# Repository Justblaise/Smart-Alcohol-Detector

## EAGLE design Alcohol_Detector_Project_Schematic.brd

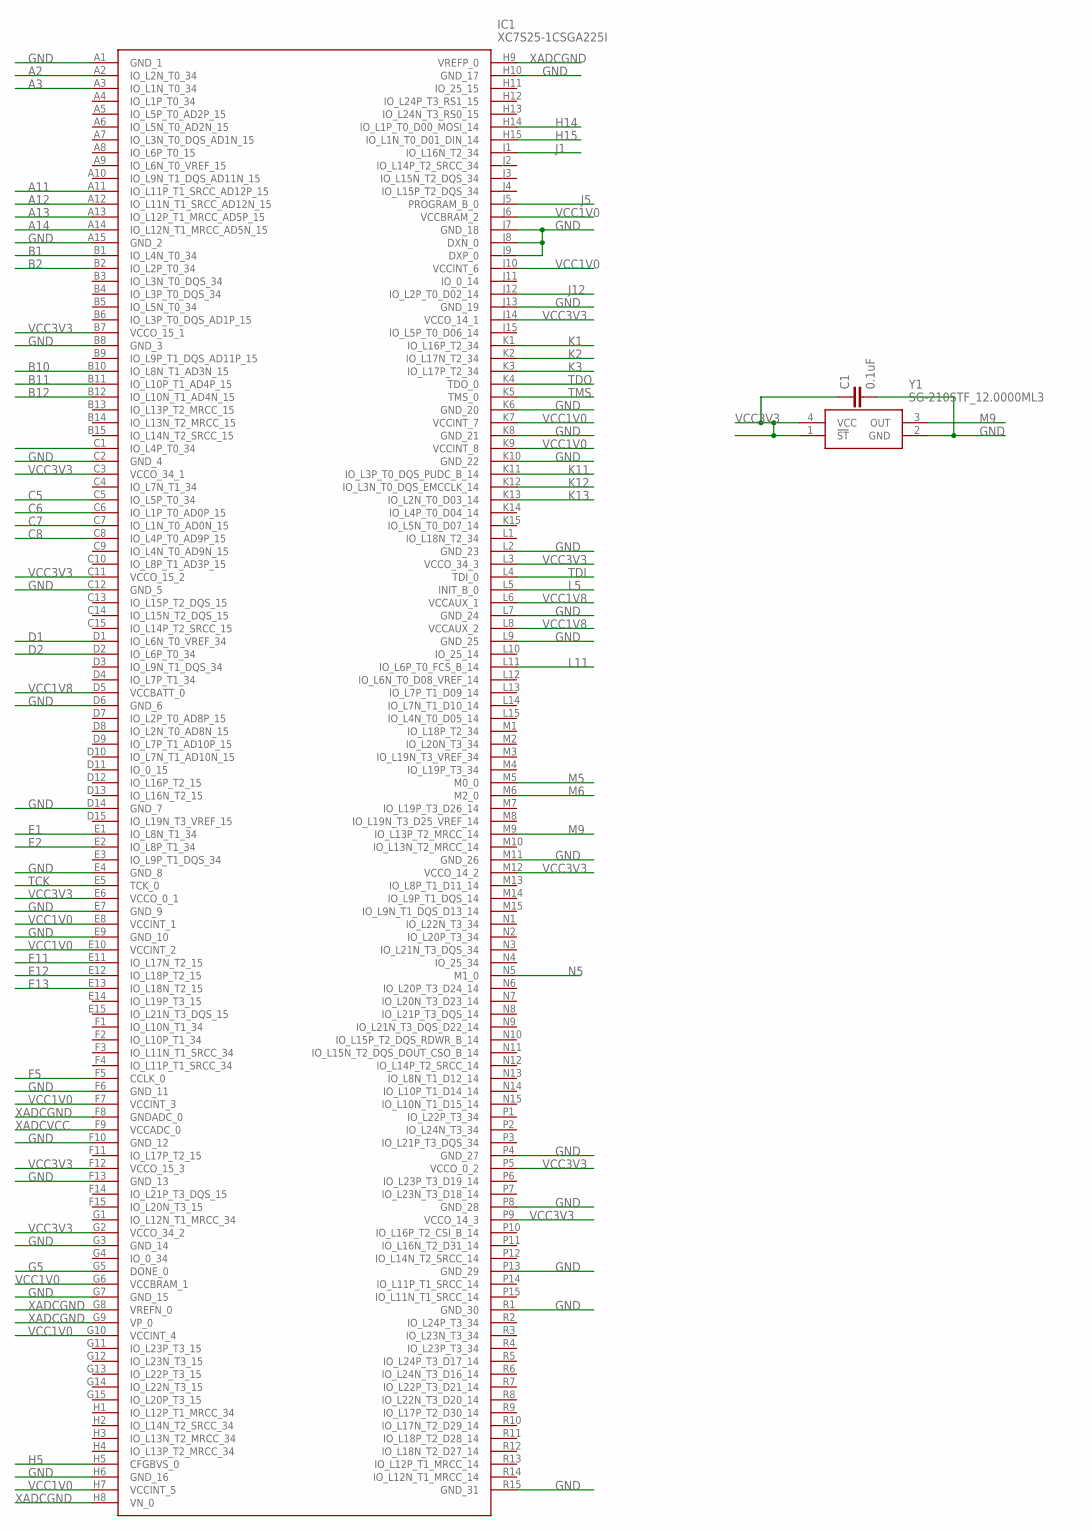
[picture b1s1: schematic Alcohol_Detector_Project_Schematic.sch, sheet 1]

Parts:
C1: 0.1uF; 0402
IC1: XC7S25-1CSGA225I; BGA225C80P15X15_1300X1300X140
Y1: SG-210STF_12.0000ML3; SG210STF120000ML3

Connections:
A2: IC1.A2 (IO_L2N_T0_34); also elsewhere on the board
A3: IC1.A3 (IO_L1N_T0_34); also elsewhere on the board
A11: IC1.A11 (IO_L11P_T1_SRCC_AD12P_15); also elsewhere on the board
A12: IC1.A12 (IO_L11N_T1_SRCC_AD12N_15); also elsewhere on the board
A13: IC1.A13 (IO_L12P_T1_MRCC_AD5P_15); also elsewhere on the board
A14: IC1.A14 (IO_L12N_T1_MRCC_AD5N_15); also elsewhere on the board
B1: IC1.B1 (IO_L4N_T0_34); also elsewhere on the board
B2: IC1.B2 (IO_L2P_T0_34); also elsewhere on the board
B10: IC1.B10 (IO_L8N_T1_AD3N_15); also elsewhere on the board
B11: IC1.B11 (IO_L10P_T1_AD4P_15); also elsewhere on the board
B12: IC1.B12 (IO_L10N_T1_AD4N_15); also elsewhere on the board
C5: IC1.C5 (IO_L5P_T0_34); also elsewhere on the board
C6: IC1.C6 (IO_L1P_T0_AD0P_15); also elsewhere on the board
C7: IC1.C7 (IO_L1N_T0_AD0N_15); also elsewhere on the board
C8: IC1.C8 (IO_L4P_T0_AD9P_15); also elsewhere on the board
D1: IC1.D1 (IO_L6N_T0_VREF_34); also elsewhere on the board
D2: IC1.D2 (IO_L6P_T0_34); also elsewhere on the board
E1: IC1.E1 (IO_L8N_T1_34); also elsewhere on the board
E2: IC1.E2 (IO_L8P_T1_34); also elsewhere on the board
E11: IC1.E11 (IO_L17N_T2_15); also elsewhere on the board
E12: IC1.E12 (IO_L18P_T2_15); also elsewhere on the board
E13: IC1.E13 (IO_L18N_T2_15); also elsewhere on the board
F5: IC1.F5 (CCLK_0); also elsewhere on the board
G5: IC1.G5 (DONE_0); also elsewhere on the board
GND: C1.2, IC1.A1 (GND_1), IC1.A15 (GND_2), IC1.B8 (GND_3), IC1.C2 (GND_4), IC1.C12 (GND_5), IC1.D6 (GND_6), IC1.D14 (GND_7), IC1.E4 (GND_8), IC1.E7 (GND_9), IC1.E9 (GND_10), IC1.F6 (GND_11), IC1.F10 (GND_12), IC1.F13 (GND_13), IC1.G3 (GND_14), IC1.G7 (GND_15), IC1.H6 (GND_16), IC1.H10 (GND_17), IC1.J7 (GND_18), IC1.J8 (DXN_0), IC1.J9 (DXP_0), IC1.J13 (GND_19), IC1.K6 (GND_20), IC1.K8 (GND_21), IC1.K10 (GND_22), IC1.L2 (GND_23), IC1.L7 (GND_24), IC1.L9 (GND_25), IC1.M11 (GND_26), IC1.P4 (GND_27), IC1.P8 (GND_28), IC1.P13 (GND_29), IC1.R1 (GND_30), IC1.R15 (GND_31), Y1.2 (GND); also elsewhere on the board
H5: IC1.H5 (CFGBVS_0); also elsewhere on the board
H14: IC1.H14 (IO_L1P_T0_D00_MOSI_14); also elsewhere on the board
H15: IC1.H15 (IO_L1N_T0_D01_DIN_14); also elsewhere on the board
J1: IC1.J1 (IO_L16N_T2_34); also elsewhere on the board
J5: IC1.J5 (PROGRAM_B_0); also elsewhere on the board
J12: IC1.J12 (IO_L2P_T0_D02_14); also elsewhere on the board
K1: IC1.K1 (IO_L16P_T2_34); also elsewhere on the board
K2: IC1.K2 (IO_L17N_T2_34); also elsewhere on the board
K3: IC1.K3 (IO_L17P_T2_34); also elsewhere on the board
K11: IC1.K11 (IO_L3P_T0_DQS_PUDC_B_14); also elsewhere on the board
K12: IC1.K12 (IO_L3N_T0_DQS_EMCCLK_14); also elsewhere on the board
K13: IC1.K13 (IO_L2N_T0_D03_14); also elsewhere on the board
L5: IC1.L5 (INIT_B_0); also elsewhere on the board
L11: IC1.L11 (IO_L6P_T0_FCS_B_14); also elsewhere on the board
M5: IC1.M5 (M0_0); also elsewhere on the board
M6: IC1.M6 (M2_0); also elsewhere on the board
M9: IC1.M9 (IO_L13P_T2_MRCC_14), Y1.3 (OUT)
N5: IC1.N5 (M1_0); also elsewhere on the board
TCK: IC1.E5 (TCK_0); also elsewhere on the board
TDI: IC1.L4 (TDI_0); also elsewhere on the board
TDO: IC1.K4 (TDO_0); also elsewhere on the board
TMS: IC1.K5 (TMS_0); also elsewhere on the board
VCC1V0: IC1.E8 (VCCINT_1), IC1.E10 (VCCINT_2), IC1.F7 (VCCINT_3), IC1.G6 (VCCBRAM_1), IC1.G10 (VCCINT_4), IC1.H7 (VCCINT_5), IC1.J6 (VCCBRAM_2), IC1.J10 (VCCINT_6), IC1.K7 (VCCINT_7), IC1.K9 (VCCINT_8); also elsewhere on the board
VCC1V8: IC1.D5 (VCCBATT_0), IC1.L6 (VCCAUX_1), IC1.L8 (VCCAUX_2); also elsewhere on the board
VCC3V3: C1.1, IC1.B7 (VCCO_15_1), IC1.C3 (VCCO_34_1), IC1.C11 (VCCO_15_2), IC1.E6 (VCCO_0_1), IC1.F12 (VCCO_15_3), IC1.G2 (VCCO_34_2), IC1.J14 (VCCO_14_1), IC1.L3 (VCCO_34_3), IC1.M12 (VCCO_14_2), IC1.P5 (VCCO_0_2), IC1.P9 (VCCO_14_3), Y1.1 (!ST), Y1.4 (VCC); also elsewhere on the board
XADCGND: IC1.F8 (GNDADC_0), IC1.G8 (VREFN_0), IC1.G9 (VP_0), IC1.H8 (VN_0), IC1.H9 (VREFP_0); also elsewhere on the board
XADCVCC: IC1.F9 (VCCADC_0); also elsewhere on the board

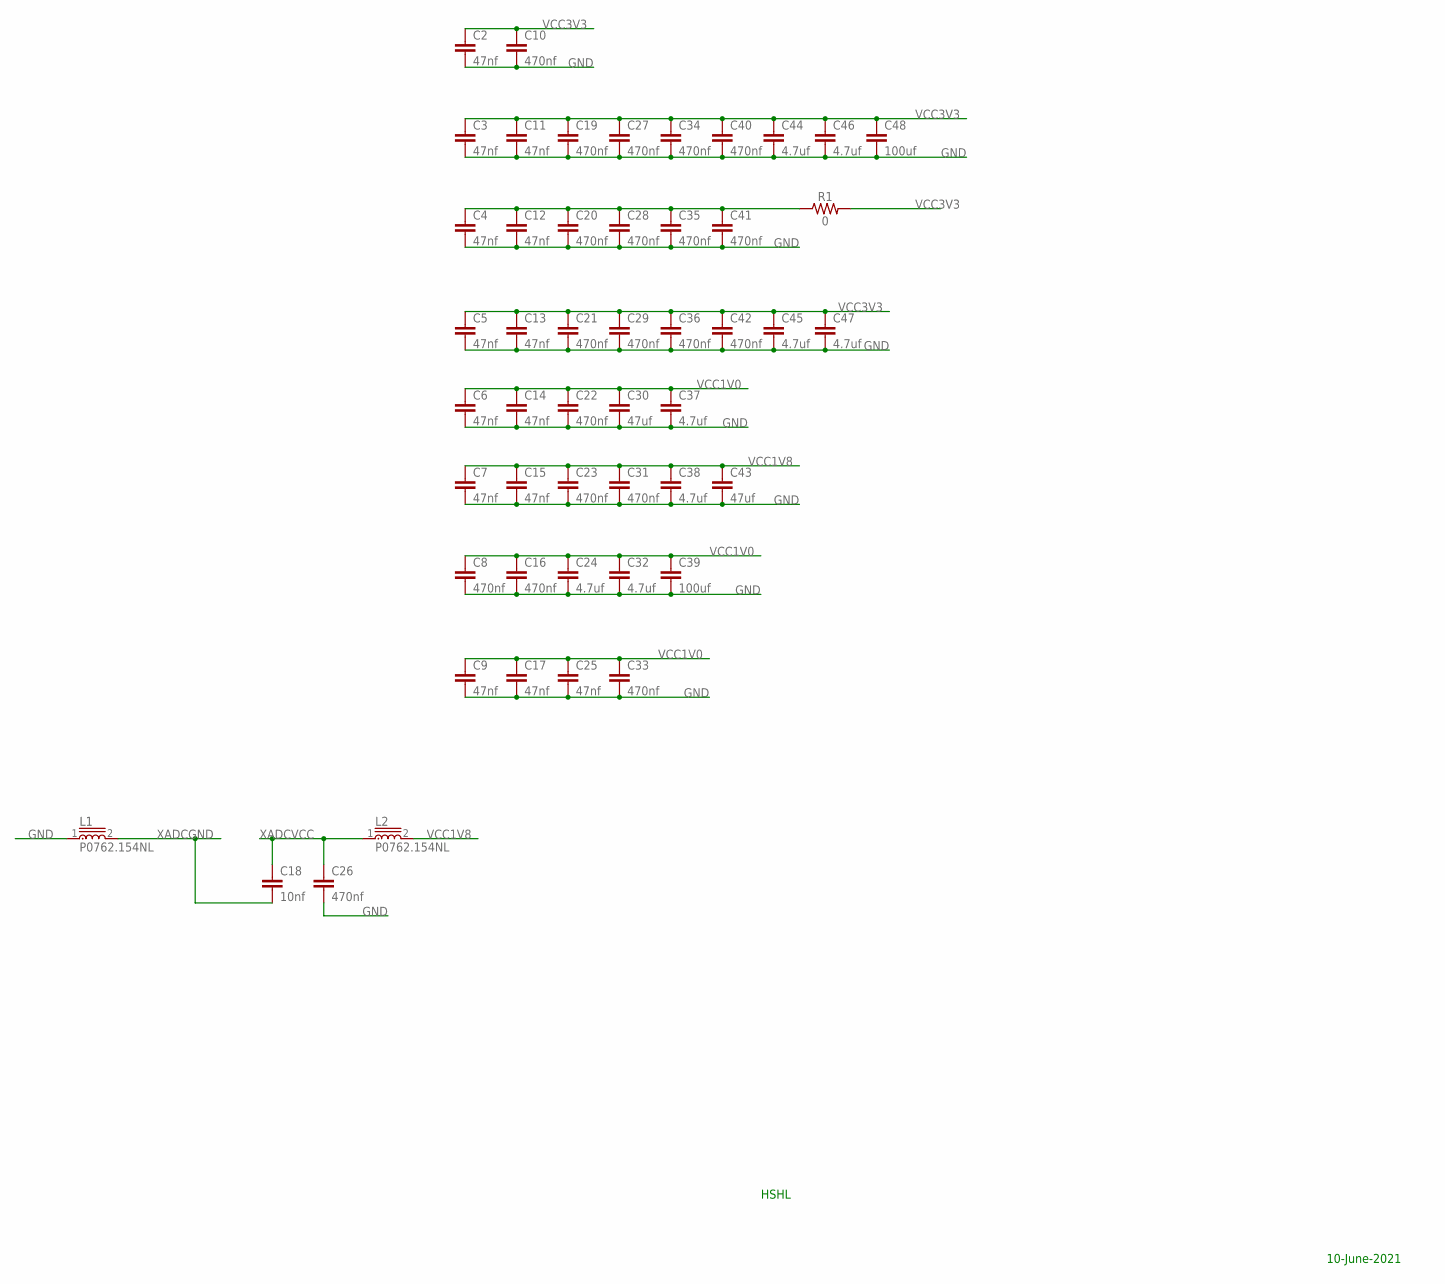
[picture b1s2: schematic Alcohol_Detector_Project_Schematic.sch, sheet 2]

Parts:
C2, C3, C4, C5, C6, C7, C9, C11, C12, C13, C14, C15, C17, C25: 47nf; C2.5-3
C8, C10, C16, C19, C20, C21, C22, C23, C26, C27, C28, C29, C31, C33, C34, C35, C36, C40, C41, C42: 470nf; C2.5-3
C18: 10nf; C2.5-3
C24, C32, C37, C38, C44, C45, C46, C47: 4.7uf; C2.5-3
C30, C43: 47uf; C2.5-3
C39, C48: 100uf; C2.5-3
L1, L2: P0762.154NL; P0762NL
R1: 0; 0402

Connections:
GND: C2.2, C3.2, C4.2, C5.2, C6.2, C7.2, C8.2, C9.2, C10.2, C11.2, C12.2, C13.2, C14.2, C15.2, C16.2, C17.2, C19.2, C20.2, C21.2, C22.2, C23.2, C24.2, C25.2, C26.2, C27.2, C28.2, C29.2, C30.2, C31.2, C32.2, C33.2, C34.2, C35.2, C36.2, C37.2, C38.2, C39.2, C40.2, C41.2, C42.2, C43.2, C44.2, C45.2, C46.2, C47.2, C48.2, L1.1; also elsewhere on the board
unnamed: C4.1, C12.1, C20.1, C28.1, C35.1, C41.1, R1.1
VCC1V0: C6.1, C8.1, C9.1, C14.1, C16.1, C17.1, C22.1, C24.1, C25.1, C30.1, C32.1, C33.1, C37.1, C39.1; also elsewhere on the board
VCC1V8: C7.1, C15.1, C23.1, C31.1, C38.1, C43.1, L2.2; also elsewhere on the board
VCC3V3: C2.1, C3.1, C5.1, C10.1, C11.1, C13.1, C19.1, C21.1, C27.1, C29.1, C34.1, C36.1, C40.1, C42.1, C44.1, C45.1, C46.1, C47.1, C48.1, R1.2; also elsewhere on the board
XADCGND: C18.2, L1.2; also elsewhere on the board
XADCVCC: C18.1, C26.1, L2.1; also elsewhere on the board

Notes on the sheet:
HSHL
10-June-2021

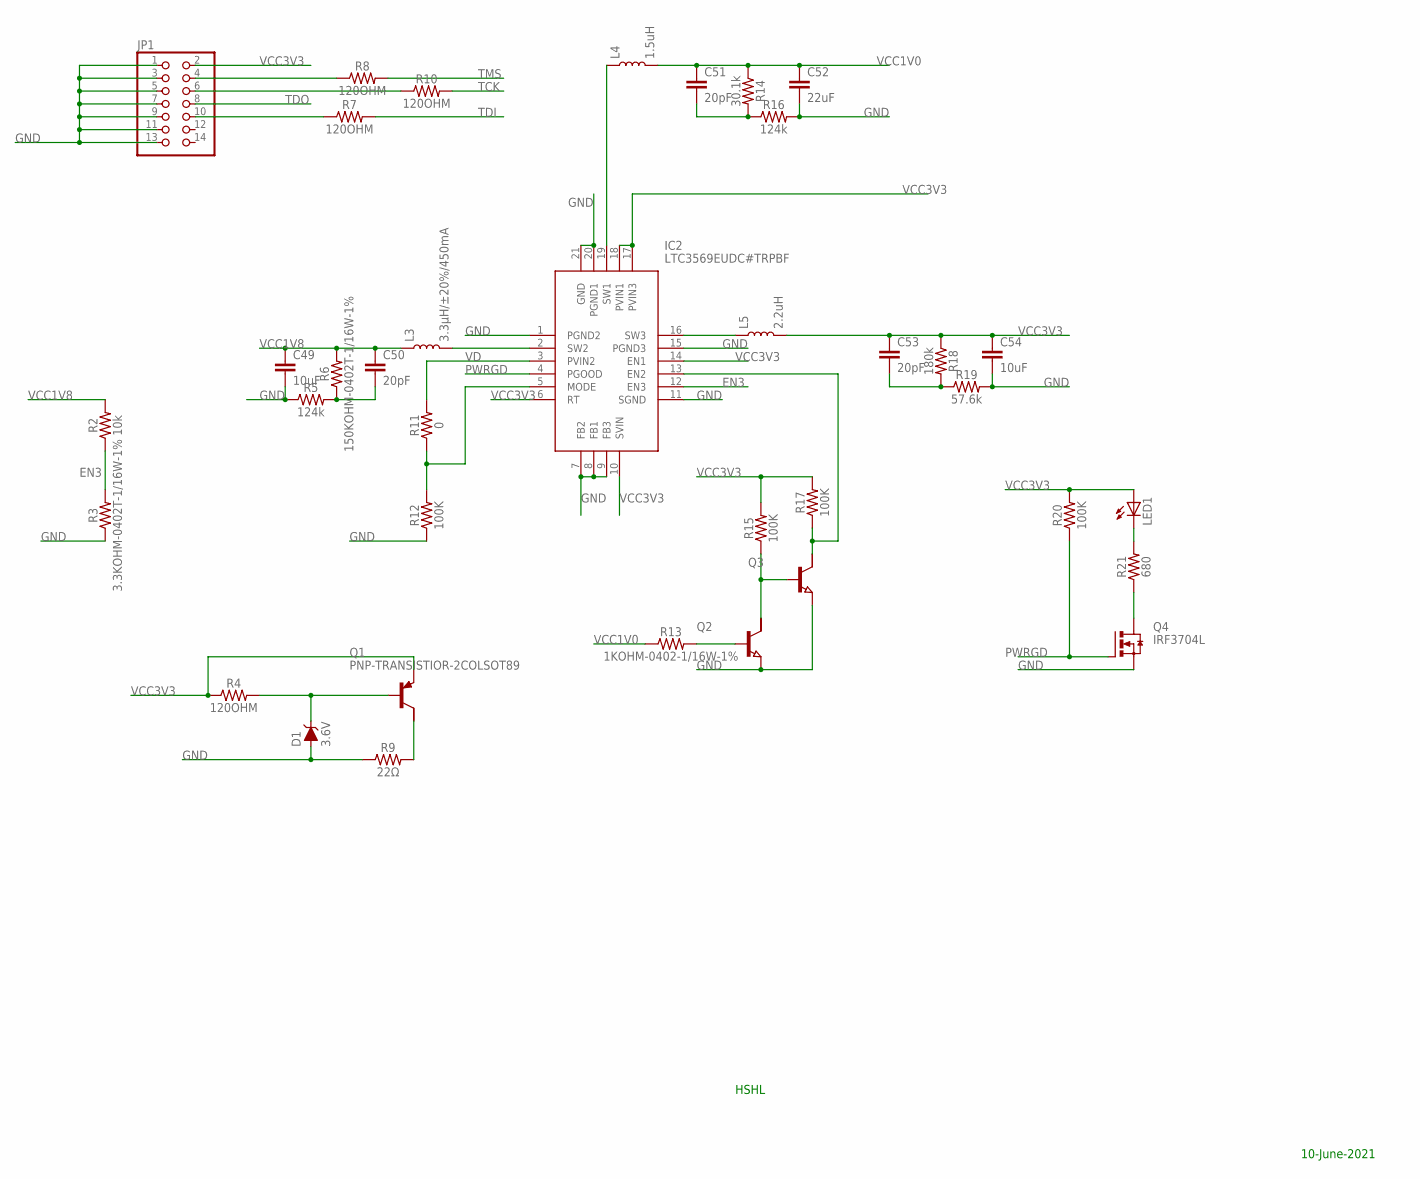
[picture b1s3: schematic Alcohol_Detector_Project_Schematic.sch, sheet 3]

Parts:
C49, C54: 10uF; 0402-TIGHT
C50, C51, C53: 20pF; 0402-TIGHT
C52: 22uF; 0603
D1: 3.6V; SOD-323
IC2: LTC3569EUDC#TRPBF; QFN50P300X400X80-21N
JP1: PINHD-2X7/90; 2X07/90
L3: 3.3µH/±20%/450mA; 0805
L4: 1.5uH; INDUCTOR_2X2
L5: 2.2uH; 0805-WIDE
LED1: LEDB152; Q62902-B152
Q1: PNP-TRANSISTIOR-2COLSOT89; SOT89
Q2, Q3: NPN-TRANSISTIOR-2COLSOT89; SOT89
Q4: IRF3704L; TO262-H
R2: 10k; 0402-TIGHT
R3: 3.3KOHM-0402T-1/16W-1%; 0402-TIGHT
R4, R7, R8, R10: 120OHM; 0603
R5, R16: 124k; 0603
R6: 150KOHM-0402T-1/16W-1%; 0402-TIGHT
R9: 22Ω; 0402
R11: 0; 0402
R12, R15, R17, R20: 100K; 0402
R13: 1KOHM-0402-1/16W-1%; 0402
R14: 30.1k; 0603
R18: 180k; 0603
R19: 57.6k; 0603
R21: 680; 0603

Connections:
EN3: IC2.12 (EN3), R2.1, R3.2
GND: C49.2, C50.2, C52.2, C53.2, C54.2, D1.A, IC2.1 (PGND2), IC2.7 (FB2), IC2.8 (FB1), IC2.9 (FB3), IC2.11 (SGND), IC2.15 (PGND3), IC2.20 (PGND1), IC2.21 (GND), JP1.1, JP1.3, JP1.5, JP1.7, JP1.9, JP1.11, JP1.13, Q2.3 (E), Q3.3 (E), Q4.3 (S), R3.1, R5.1, R5.2, R6.1, R9.1, R12.1, R16.2, R18.2, R19.1, R19.2; also elsewhere on the board
unnamed: IC2.19 (SW1), L4.P$1 (1)
unnamed: IC2.2 (SW2), L3.2
unnamed: C51.2, R14.2, R16.1
unnamed: IC2.16 (SW3), L5.1
unnamed: IC2.5 (MODE), R11.1, R12.2
unnamed: LED1.K (C), R21.2
unnamed: Q2.2 (C), Q3.1 (B), R15.1
unnamed: IC2.13 (EN2), Q3.2 (C), R17.1
unnamed: Q2.1 (B), R13.2
unnamed: Q4.2 (D), R21.1
unnamed: D1.C, Q1.1 (B), R4.2
unnamed: Q1.2 (C), R9.2
unnamed: JP1.4, R8.1
unnamed: JP1.6, R10.1
unnamed: JP1.10, R7.1
PWRGD: IC2.4 (PGOOD), Q4.1 (G), R20.1
TCK: R10.2; also elsewhere on the board
TDI: R7.2; also elsewhere on the board
TDO: JP1.8; also elsewhere on the board
TMS: R8.2; also elsewhere on the board
VCC1V0: C51.1, C52.1, L4.P$2 (2), R13.1, R14.1; also elsewhere on the board
VCC1V8: C49.1, C50.1, L3.1, R2.2, R6.2; also elsewhere on the board
VCC3V3: C53.1, C54.1, IC2.6 (RT), IC2.10 (SVIN), IC2.14 (EN1), IC2.17 (PVIN3), IC2.18 (PVIN1), JP1.2, L5.2, LED1.A, Q1.3 (E), R4.1, R15.2, R17.2, R18.1, R20.2; also elsewhere on the board
VD: IC2.3 (PVIN2), R11.2

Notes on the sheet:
HSHL
10-June-2021

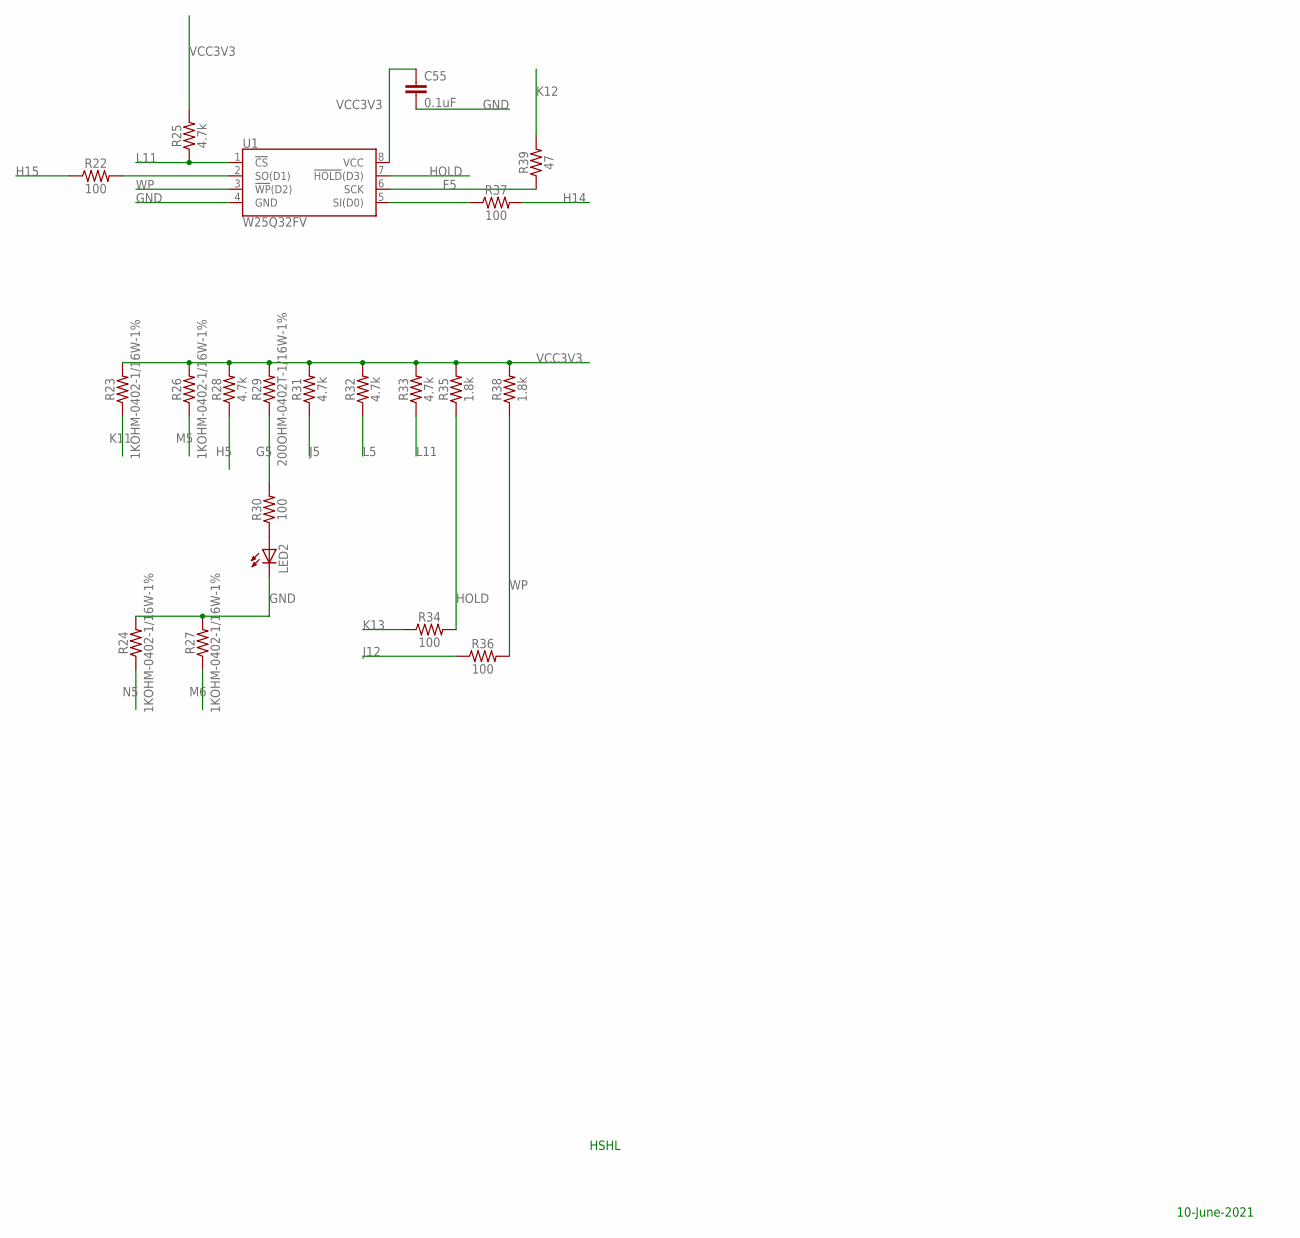
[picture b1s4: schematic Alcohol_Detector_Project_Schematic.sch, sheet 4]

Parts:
C55: 0.1uF; 0402
LED2: LEDB152; Q62902-B152
R22, R30, R34, R36, R37: 100; 0603
R23, R24, R26, R27: 1KOHM-0402-1/16W-1%; 0402
R25, R28, R31, R32, R33: 4.7k; 0402-TIGHT
R29: 200OHM-0402T-1/16W-1%; 0402-TIGHT
R35, R38: 1.8k; 0603
R39: 47; 0603
U1: W25Q32FV; SOIC-8

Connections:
F5: R39.1, U1.6 (SCK); also elsewhere on the board
G5: R29.1, R30.2; also elsewhere on the board
GND: C55.2, LED2.K (C), R24.2, R27.2, U1.4 (GND); also elsewhere on the board
H5: R28.1; also elsewhere on the board
H14: R37.2; also elsewhere on the board
H15: R22.1; also elsewhere on the board
HOLD: R34.2, R35.1, U1.7 (!HOLD!(D3))
J5: R31.1; also elsewhere on the board
J12: R36.1; also elsewhere on the board
K11: R23.1; also elsewhere on the board
K12: R39.2; also elsewhere on the board
K13: R34.1; also elsewhere on the board
L5: R32.1; also elsewhere on the board
L11: R25.1, R33.1, U1.1 (!CS!); also elsewhere on the board
M5: R26.1; also elsewhere on the board
M6: R27.1; also elsewhere on the board
N5: R24.1; also elsewhere on the board
unnamed: LED2.A, R30.1
unnamed: R22.2, U1.2 (SO(D1))
unnamed: R37.1, U1.5 (SI(D0))
VCC3V3: C55.1, R23.2, R25.2, R26.2, R28.2, R29.2, R31.2, R32.2, R33.2, R35.2, R38.2, U1.8 (VCC); also elsewhere on the board
WP: R36.2, R38.1, U1.3 (!WP!(D2))

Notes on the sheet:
HSHL
10-June-2021

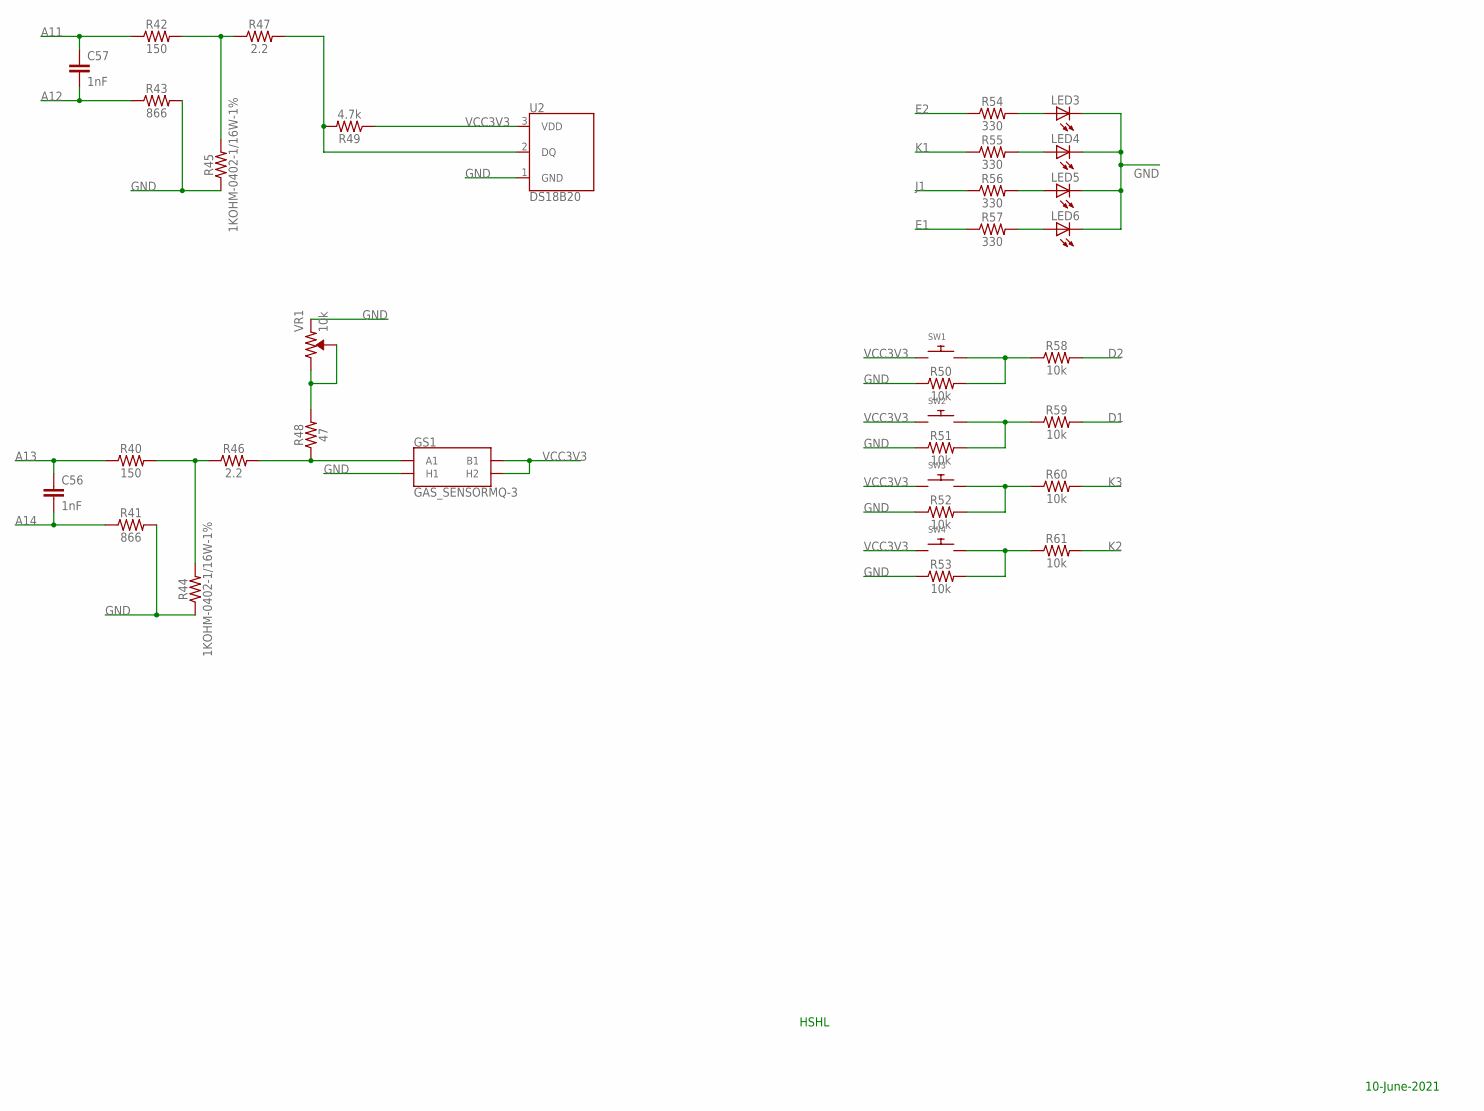
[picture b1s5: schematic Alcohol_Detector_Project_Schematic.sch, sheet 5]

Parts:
C56, C57: 1nF; 0402
GS1: GAS_SENSORMQ-3; GAS_SENSOR
LED3, LED4, LED5, LED6: LEDB152; Q62902-B152
R40, R42: 150; 0603
R41, R43: 866; 0603
R44, R45: 1KOHM-0402-1/16W-1%; 0402
R46, R47: 2.2; 0603
R48: 47; 0603
R49: 4.7k; 0402-TIGHT
R50, R51, R52, R53, R58, R59, R60, R61: 10k; 0402
R54, R55, R56, R57: 330; 0402
SW1, SW2, SW3, SW4: SWITCH_PUSHBUTTONC&K_KSS; BTN_CK_KSS
U2: DS18B20; TO-92-AMMO
VR1: 10k; TRIMPOT-PTH-3386U

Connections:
A11: C57.1, R42.1; also elsewhere on the board
A12: C57.2, R43.1; also elsewhere on the board
A13: C56.1, R40.1; also elsewhere on the board
A14: C56.2, R41.1; also elsewhere on the board
D1: R59.2; also elsewhere on the board
D2: R58.2; also elsewhere on the board
E1: R57.1; also elsewhere on the board
E2: R54.1; also elsewhere on the board
GND: GS1.HA (H1), LED3.K (C), LED4.K (C), LED5.K (C), LED6.K (C), R41.2, R43.2, R44.1, R45.1, R50.1, R51.1, R52.1, R53.1, U2.1 (GND), VR1.1 (CCW); also elsewhere on the board
J1: R56.1; also elsewhere on the board
K1: R55.1; also elsewhere on the board
K2: R61.2; also elsewhere on the board
K3: R60.2; also elsewhere on the board
unnamed: GS1.A1, R46.2, R48.1
unnamed: R42.2, R45.2, R47.1
unnamed: R40.2, R44.2, R46.1
unnamed: R50.2, R58.1, SW1.P$2
unnamed: LED3.A, R54.2
unnamed: R51.2, R59.1, SW2.P$2
unnamed: R48.2, VR1.2 (WIPER), VR1.3 (CW)
unnamed: LED4.A, R55.2
unnamed: R52.2, R60.1, SW3.P$2
unnamed: LED5.A, R56.2
unnamed: R47.2, R49.2, U2.2 (DQ)
unnamed: R53.2, R61.1, SW4.P$2
unnamed: LED6.A, R57.2
VCC3V3: GS1.B1, GS1.HB (H2), R49.1, SW1.P$1, SW2.P$1, SW3.P$1, SW4.P$1, U2.3 (VDD); also elsewhere on the board

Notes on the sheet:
HSHL
10-June-2021

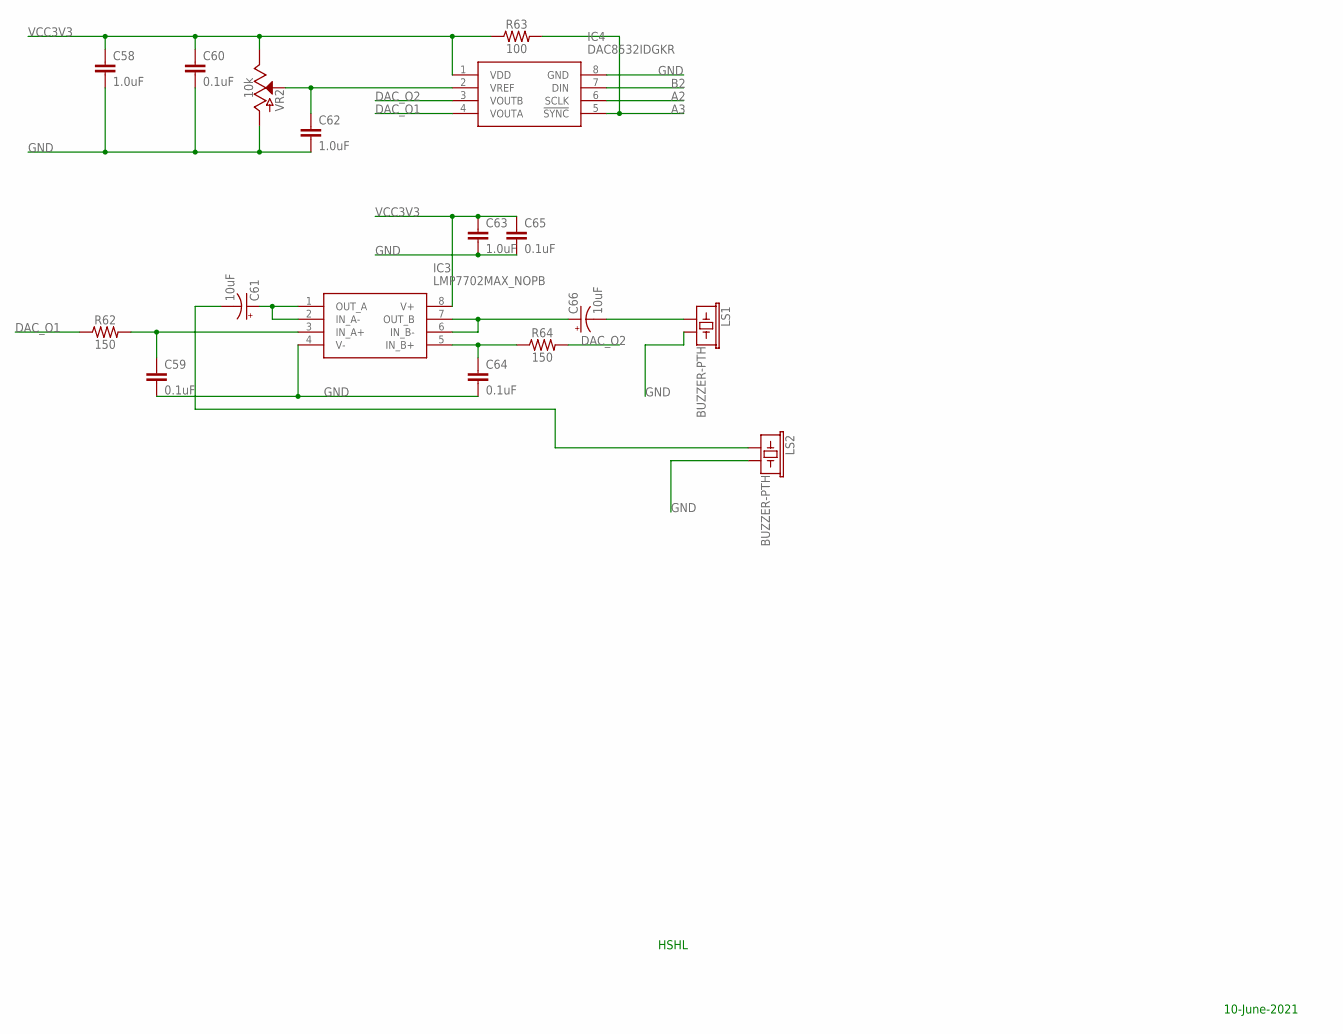
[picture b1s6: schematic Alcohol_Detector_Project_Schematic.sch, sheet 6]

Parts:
C58, C62, C63: 1.0uF; 0402
C59, C60, C64, C65: 0.1uF; 0402
C61, C66: 10uF; 0603-POLAR
IC3: LMP7702MAX_NOPB; SOIC127P600X175-8N
IC4: DAC8532IDGKR; SOP65P490X110-8N
LS1, LS2: BUZZER-PTH; BUZZER-12MM
R62, R64: 150; 0603
R63: 100; 0603
VR2: 10k; SLIDER-SMALL

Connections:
A2: IC4.6 (SCLK); also elsewhere on the board
A3: IC4.5 (!SYNC), R63.2; also elsewhere on the board
B2: IC4.7 (DIN); also elsewhere on the board
DAC_O1: IC4.4 (VOUTA), R62.1
DAC_O2: IC4.3 (VOUTB), R64.2
GND: C58.2, C59.2, C60.2, C62.2, C63.2, C64.2, C65.2, IC3.4 (V-), IC4.8 (GND), LS1.- (2), LS2.- (2), VR2.BOTTOM (A); also elsewhere on the board
unnamed: C62.1, IC4.2 (VREF), VR2.WIPER (S)
unnamed: C66.+, IC3.6 (IN_B-), IC3.7 (OUT_B)
unnamed: C64.1, IC3.5 (IN_B+), R64.1
unnamed: C59.1, IC3.3 (IN_A+), R62.2
unnamed: C61.+, IC3.1 (OUT_A), IC3.2 (IN_A-)
unnamed: C66.-, LS1.+ (1)
unnamed: C61.-, LS2.+ (1)
VCC3V3: C58.1, C60.1, C63.1, C65.1, IC3.8 (V+), IC4.1 (VDD), R63.1, VR2.TOP (E); also elsewhere on the board

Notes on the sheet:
HSHL
10-June-2021

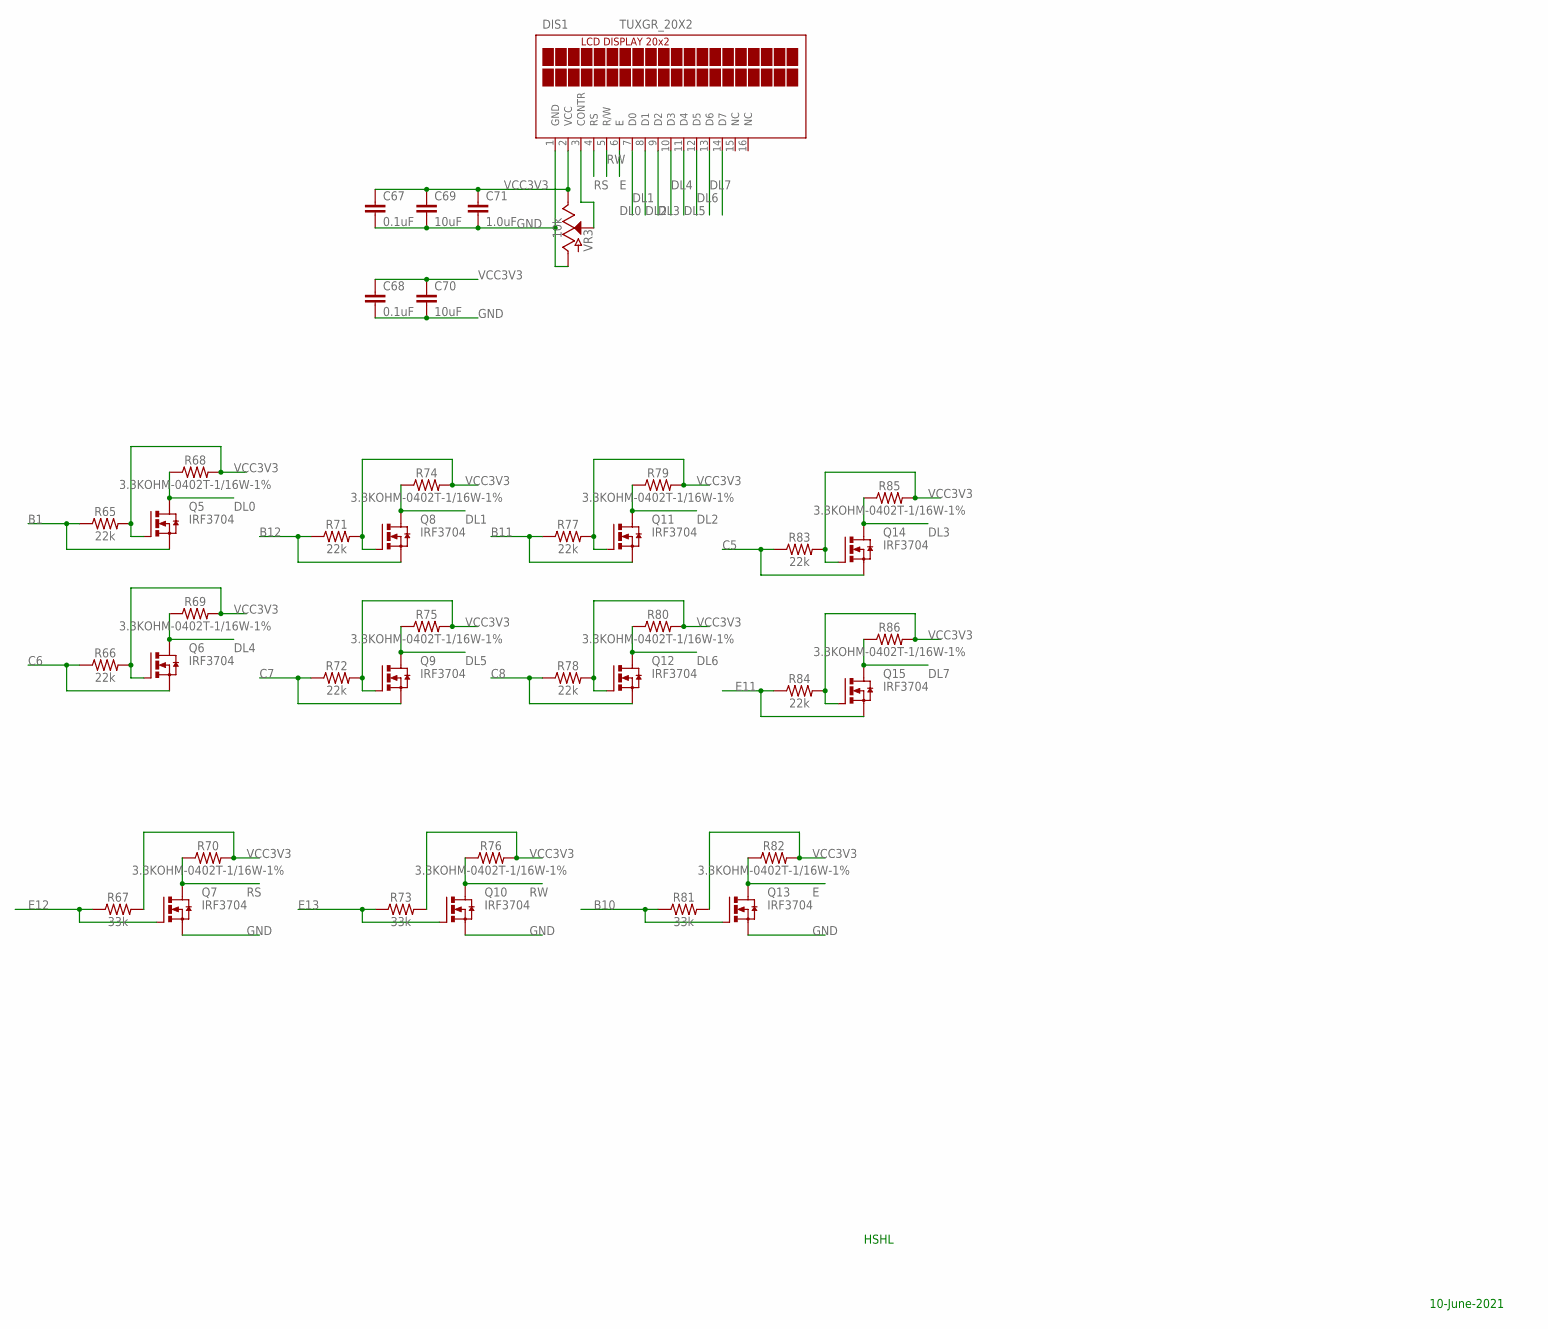
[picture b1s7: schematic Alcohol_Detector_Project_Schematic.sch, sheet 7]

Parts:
C67, C68: 0.1uF; 0402
C69, C70: 10uF; 0402-TIGHT
C71: 1.0uF; 0402
DIS1: TUXGR_20X2
Q5, Q6, Q7, Q8, Q9, Q10, Q11, Q12, Q13, Q14, Q15: IRF3704; TO220AH
R65, R66, R71, R72, R77, R78, R83, R84: 22k; 0402-TIGHT
R67, R73, R81: 33k; 0402-TIGHT
R68, R69, R70, R74, R75, R76, R79, R80, R82, R85, R86: 3.3KOHM-0402T-1/16W-1%; 0402-TIGHT
VR3: 10k; SLIDER-SMALL

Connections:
B1: Q5.E (S), R65.1; also elsewhere on the board
B10: Q13.B (G), R81.1; also elsewhere on the board
B11: Q11.E (S), R77.1; also elsewhere on the board
B12: Q8.E (S), R71.1; also elsewhere on the board
C5: Q14.E (S), R83.1; also elsewhere on the board
C6: Q6.E (S), R66.1; also elsewhere on the board
C7: Q9.E (S), R72.1; also elsewhere on the board
C8: Q12.E (S), R78.1; also elsewhere on the board
DL0: DIS1.7 (D0), Q5.C (D), R68.1
DL1: DIS1.8 (D1), Q8.C (D), R74.1
DL2: DIS1.9 (D2), Q11.C (D), R79.1
DL3: DIS1.10 (D3), Q14.C (D), R85.1
DL4: DIS1.11 (D4), Q6.C (D), R69.1
DL5: DIS1.12 (D5), Q9.C (D), R75.1
DL6: DIS1.13 (D6), Q12.C (D), R80.1
DL7: DIS1.14 (D7), Q15.C (D), R86.1
E: DIS1.6 (E), Q13.C (D), R82.1
E11: Q15.E (S), R84.1; also elsewhere on the board
E12: Q7.B (G), R67.1; also elsewhere on the board
E13: Q10.B (G), R73.1; also elsewhere on the board
GND: C67.2, C68.2, C69.2, C70.2, C71.2, DIS1.1 (GND), Q7.E (S), Q10.E (S), Q13.E (S), VR3.BOTTOM (A); also elsewhere on the board
unnamed: DIS1.3 (CONTR), VR3.WIPER (S)
RS: DIS1.4 (RS), Q7.C (D), R70.1
RW: DIS1.5 (R/W), Q10.C (D), R76.1
VCC3V3: C67.1, C68.1, C69.1, C70.1, C71.1, DIS1.2 (VCC), Q5.B (G), Q6.B (G), Q8.B (G), Q9.B (G), Q11.B (G), Q12.B (G), Q14.B (G), Q15.B (G), R65.2, R66.2, R67.2, R68.2, R69.2, R70.2, R71.2, R72.2, R73.2, R74.2, R75.2, R76.2, R77.2, R78.2, R79.2, R80.2, R81.2, R82.2, R83.2, R84.2, R85.2, R86.2, VR3.TOP (E); also elsewhere on the board

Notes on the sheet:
HSHL
10-June-2021

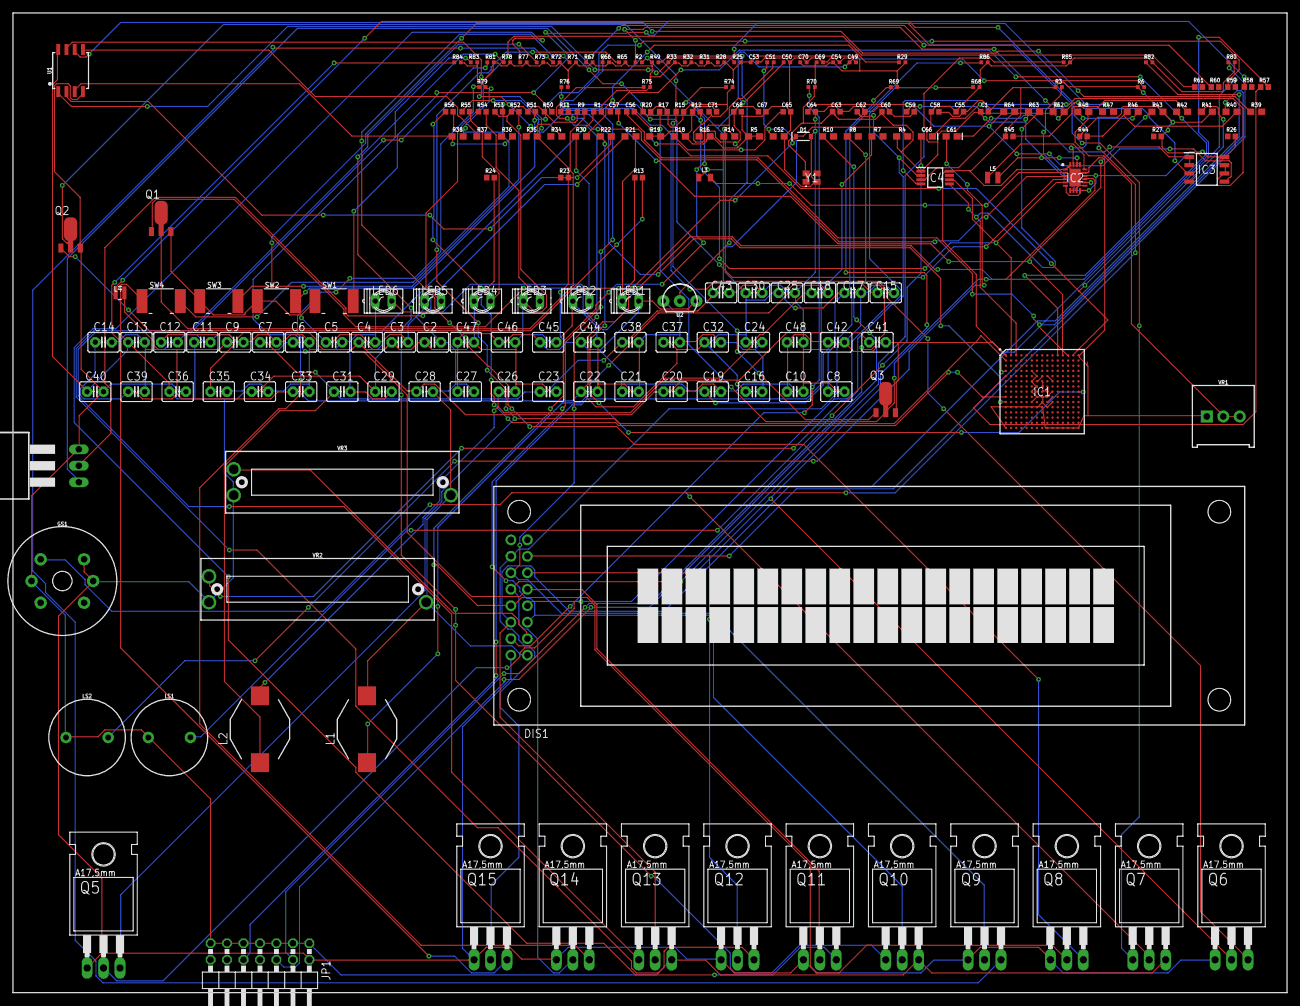
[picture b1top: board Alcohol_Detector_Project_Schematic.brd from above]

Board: 12 copper layers, 196.5 x 151.1 mm, 203 parts (0 on the bottom side), 110 nets.

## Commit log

2021-12-05 Entries

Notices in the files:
parts and their libraries:
SparkFun-Capacitors: Licensing: Creative Commons ShareAlike 4.0 International - https://creativecommons.org/licenses/by-sa/4.0
